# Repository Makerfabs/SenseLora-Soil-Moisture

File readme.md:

SenseLora Soil Moisture
```c++
/*
Version:	    V1.0
Author:		    Yuki
Create Date:	2024/11/20
Note:
*/
```

# Makerfabs

[Makerfabs home page](https://www.makerfabs.com/)

[Makerfabs Wiki](https://wiki.makerfabs.com/)

## Intruduce

Product Link:[SenseLora Soil Moisture](https://www.makerfabs.com/senselora-soil-moisture.html)

Wiki Link : [SenseLora Soil Moisture](https://wiki.makerfabs.com/SenseLora_Soil_Moisture.html)

## Features

Specs:
- ESP32-S3 WROOM module onboard with the WiFi and Bluetooth.
- Detection of soil moisture.
- Arduino Compatible: You can play it with Arduino IDE.
- Onboard LoRa module (433Mhz or 868Mhz or 915Mhz)
- Completely sealed.
- Dustproof waterproof level:IP68.
- Power by 3.7V battery.
- On board MPTT battery charger by solar panel.

# Usage

1.[Usage with LoRa Receiver](https://wiki.makerfabs.com/SenseLora_Soil_Moisture.html#4-usage-with-lora-receiver)

The Lora receiver work with SenseLora modules, it receive LoRa signal around and forward to computer, so the data can be display/record/analyze on PC.

2.[Usage with 4G Gateway](https://wiki.makerfabs.com/SenseLora_Soil_Moisture.html#5-usage-with-4g-gateway)

The 4G LTE CAT1 Gateway work with SenseLora modules, it get the LoRa data and then transmit the data via 4G to cloud server such as TTN, or the monitors phone with SMS.  

## Example

### firmware

Factory test program

### Send data to datacake

Using the Senselora 4G gateway to transfer data to the datacake platform.

### Send data to thingspeak

Using the Senselora 4G gateway to transfer data to the thingspeak platform.

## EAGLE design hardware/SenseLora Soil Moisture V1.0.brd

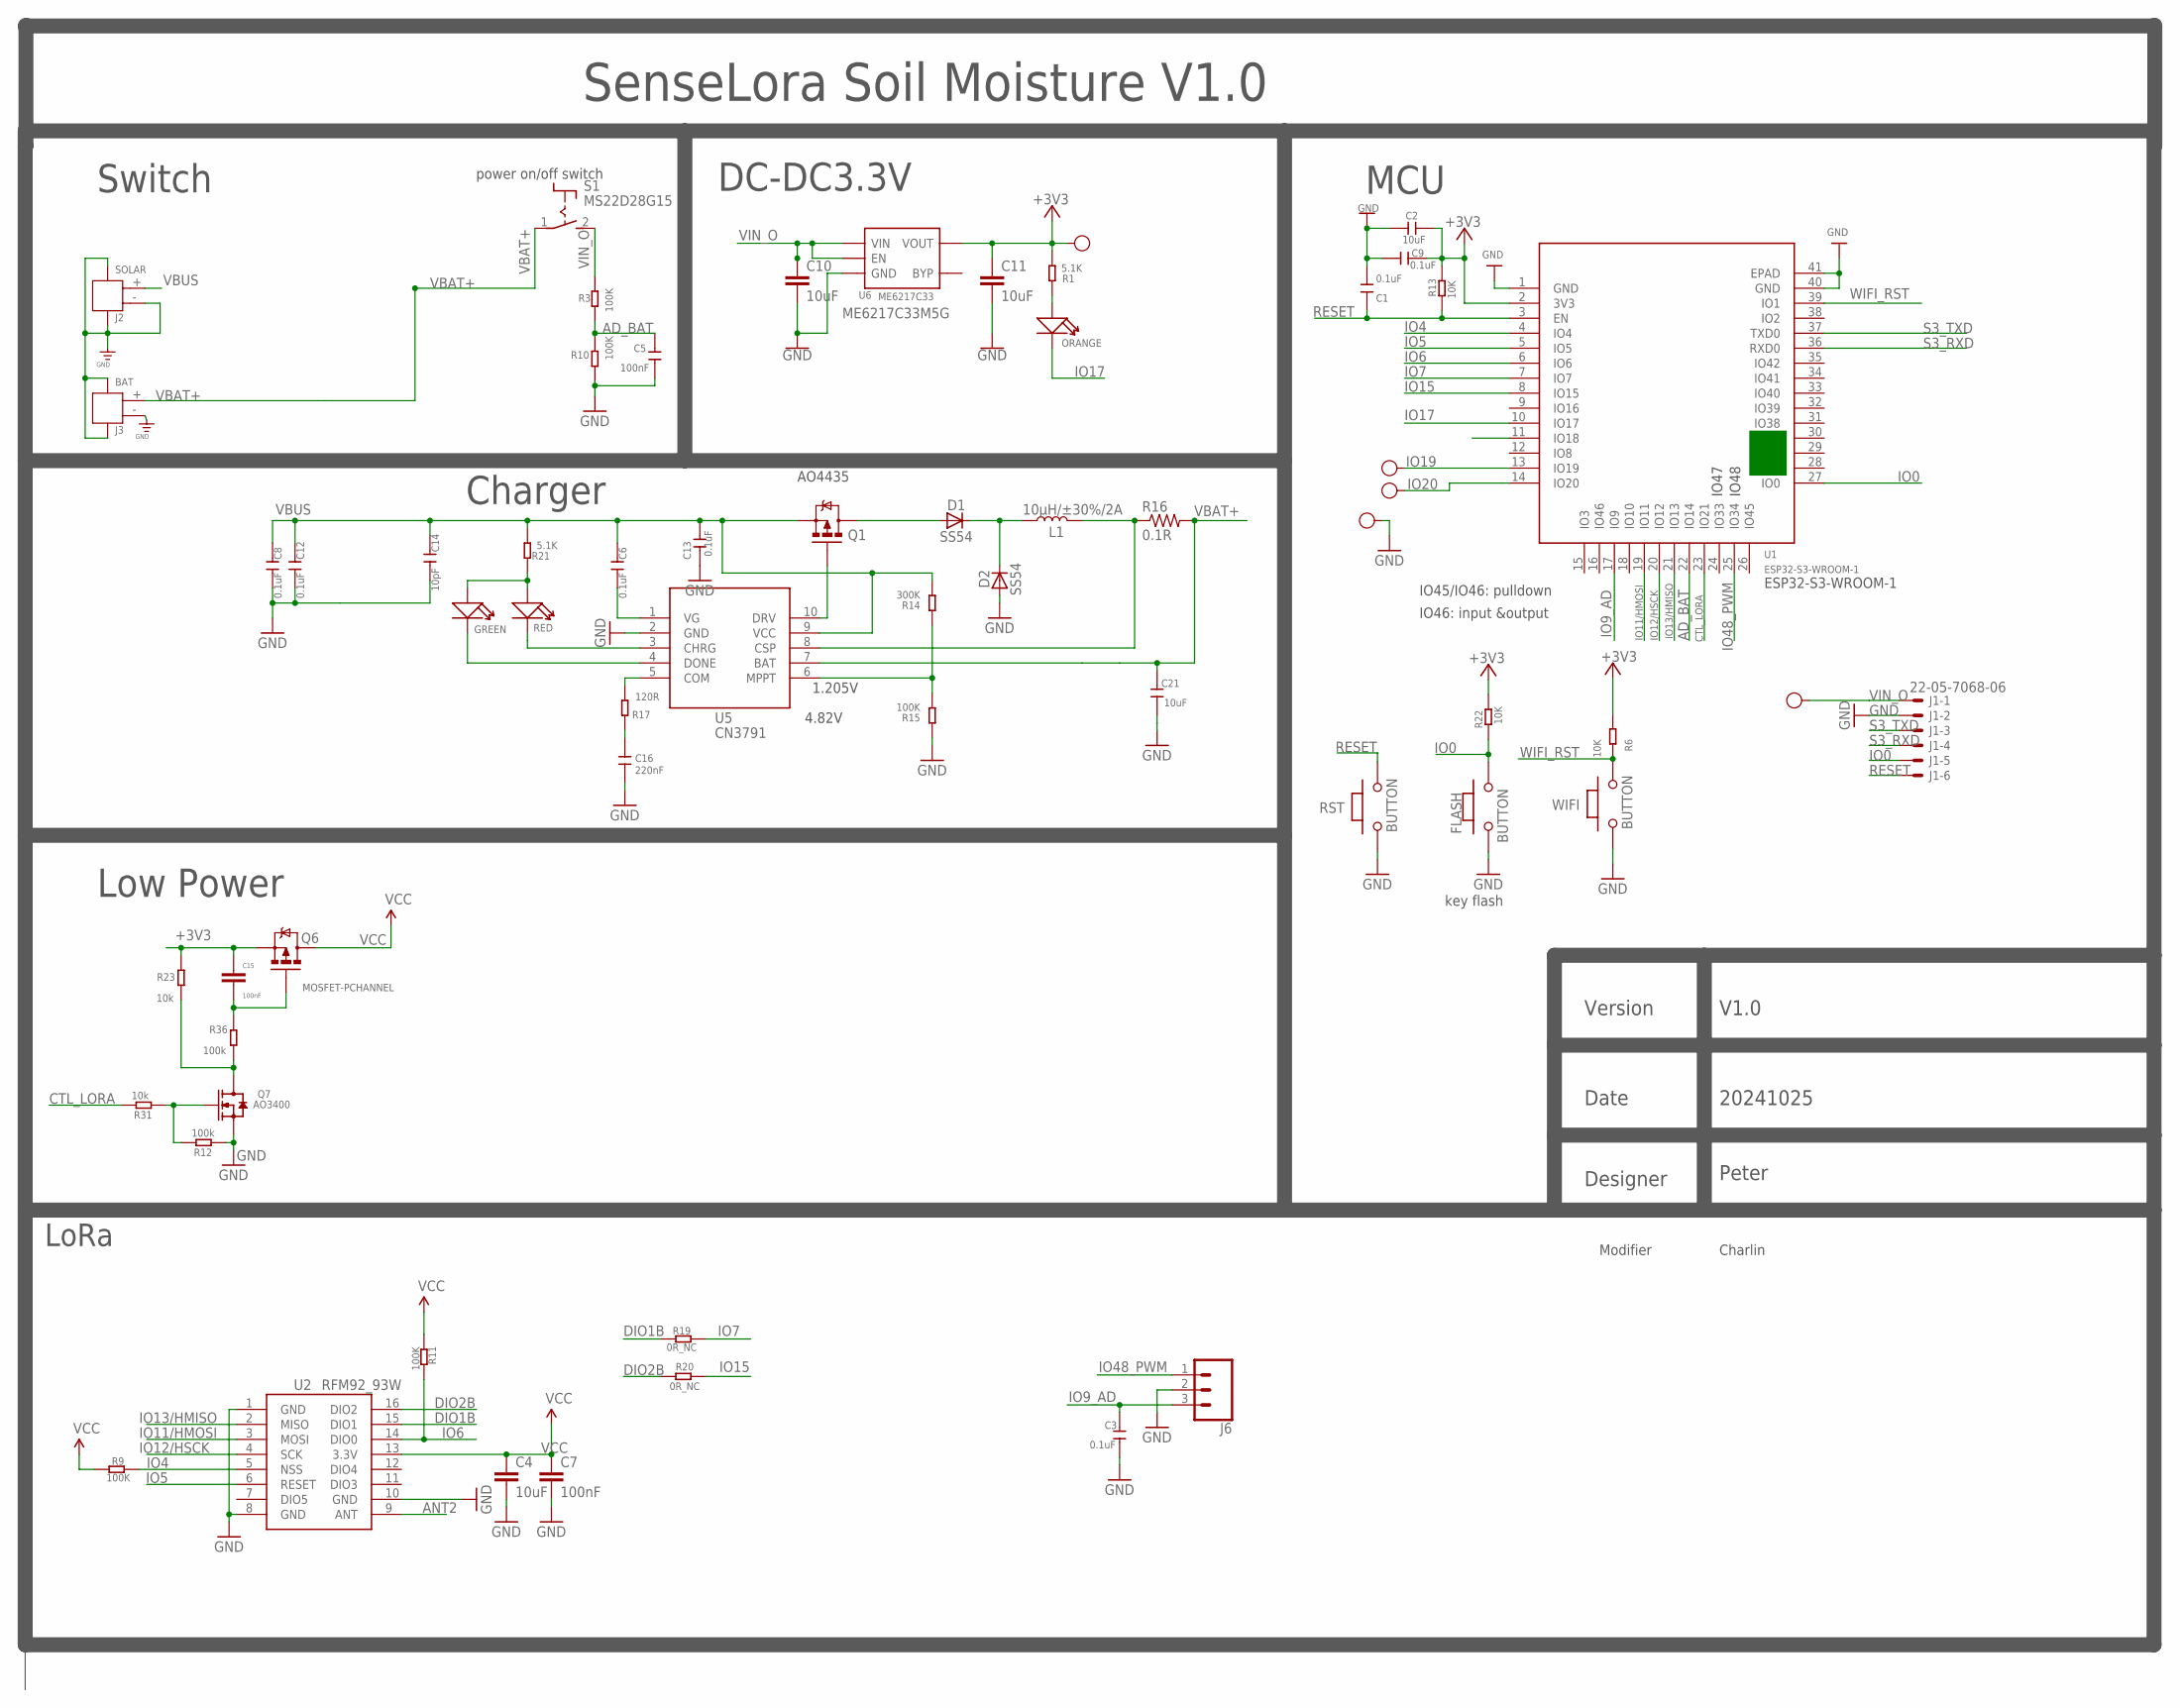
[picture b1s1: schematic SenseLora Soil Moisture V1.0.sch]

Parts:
3V3: TEST-POINT'4545'; TP-D45MIL; PARTNO DNP
C1, C3, C6, C8, C9, C12, C13: 0.1uF; DISCRETE_C0603
C2, C21: 10uF; DISCRETE_C0603
C4, C10, C11: 10uF; C0603
C5, C7, C15: 100nF; C0603
C14: 10pF; DISCRETE_C0603
C16: 220nF; DISCRETE_C0603
CHRG: RED; LED-0603
D1, D2: SS54; DO-214AC
D+: TEST-POINT'4545'; TP-D45MIL; PARTNO DNP
D-: TEST-POINT'4545'; TP-D45MIL; PARTNO DNP
DONE: GREEN; LED-0603
FLASH: BUTTON; 157SW
GND: TEST-POINT'4545'; TP-D45MIL; PARTNO DNP
J1: 22-05-7068-06; 7395-06
J2: SOLAR; HW2-SMD-2.0-90D
J3: BAT; HW2-SMD-2.0-90D
J6: CONN_03SCREW; SCREWTERMINAL-3.5MM-3
L1: 10µH/±30%/2A; CR54
Q1: MOSFET-PCHANNELFDS6675; SO08
Q6: MOSFET-PCHANNEL; SOT23-3
Q7: AO3400; SOT23@1
R1, R21: 5.1K; DISCRETE_R0603
R3, R9, R10, R11: 100K; R0603
R6, R13, R22: 10K; R0603
R12, R36: 100k; R0603
R14: 300K; DISCRETE_R0603
R15: 100K; DISCRETE_R0603
R16: 0.1R; R1206
R17: 120R; DISCRETE_R0603
R19, R20: 0R_NC; R0603
R23, R31: 10k; R0603
RST: BUTTON; 157SW
S1: MS22D28G15; S-MS22D28G15
STA: ORANGE; LED-0603
U1: ESP32-S3-WROOM-1; ESP32-­S2-­SOLO
U2: RFM92_93W
U5: CN3791; SSOP-10-150MIL
U6: ME6217C33; SOT23-5
VI: HP; TP-D45MIL; PARTNO DNP
WIFI: BUTTON; 157SW

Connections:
+3V3: 3V3.T, C2.1, C9.1, C11.1, C15.1, Q6.2 (S), R1.2, R6.2, R13.2, R22.2, R23.2, U1.2 (3V3), U6.5 (VOUT)
AD_BAT: C5.1, R3.2, R10.1, U1.22 (IO14)
ANT2: U2.9 (ANT)
CTL_LORA: R31.2, U1.23 (IO21)
DIO1B: R19.2, U2.15 (DIO1)
DIO2B: R20.2, U2.16 (DIO2)
GND: C1.2, C2.2, C3.2, C4.2, C5.2, C7.2, C8.2, C9.2, C10.2, C11.2, C12.2, C13.1, C14.2, C16.2, C21.2, D2.A, FLASH.1, GND.T, J1.2, J2.3, J2.4, J2.- (2), J3.3, J3.4, J3.- (2), J6.2, Q7.2 (S), R10.2, R12.1, R15.1, RST.1, U1.1 (GND), U1.40 (GND), U1.41 (EPAD), U2.1 (GND), U2.8 (GND), U2.10 (GND), U5.2 (GND), U6.2 (GND), WIFI.1
IO0: FLASH.2, J1.5, R22.1, U1.27 (IO0)
IO4: R9.1, U1.4 (IO4), U2.5 (NSS)
IO5: U1.5 (IO5), U2.6 (RESET)
IO6: R11.1, U1.6 (IO6), U2.14 (DIO0)
IO7: R19.1, U1.7 (IO7)
IO9_AD: C3.1, J6.3, U1.17 (IO9)
IO11/HMOSI: U1.19 (IO11), U2.3 (MOSI)
IO12/HSCK: U1.20 (IO12), U2.4 (SCK)
IO13/HMISO: U1.21 (IO13), U2.2 (MISO)
IO15: R20.1, U1.8 (IO15)
IO17: STA.-, U1.10 (IO17)
IO19: D-.T, U1.13 (IO19)
IO20: D+.T, U1.14 (IO20)
IO48_PWM: J6.1, U1.25 (IO34)
unnamed: R14.1, R15.2, U5.6 (MPPT)
unnamed: Q1.4 (G), U5.10 (DRV)
unnamed: C6.2, U5.1 (VG)
unnamed: D1.C, D2.C, L1.P$1 (1)
unnamed: D1.A, Q1.5 (D), Q1.6 (D), Q1.7 (D), Q1.8 (D)
unnamed: CHRG.+, DONE.+, R21.1
unnamed: DONE.-, U5.4 (DONE)
unnamed: CHRG.-, U5.3 (CHRG)
unnamed: R17.2, U5.5 (COM)
unnamed: C16.1, R17.1
unnamed: R1.1, STA.+
unnamed: C15.2, Q6.1 (G), R36.2
unnamed: Q7.1 (G), R12.2, R31.1
unnamed: L1.P$2 (2), R16.1, U5.8 (CSP)
unnamed: Q7.3 (D), R23.1, R36.1
RESET: C1.1, J1.6, R13.1, RST.2, U1.3 (EN)
S3_RXD: J1.4, U1.36 (RXD0)
S3_TXD: J1.3, U1.37 (TXD0)
VBAT+: C21.1, J3.+ (1), R16.2, S1.1, U5.7 (BAT)
VBUS: C6.1, C8.1, C12.1, C13.2, C14.1, J2.+ (1), Q1.1 (S), Q1.2 (S), Q1.3 (S), R14.2, R21.2, U5.9 (VCC)
VCC: C4.1, C7.1, Q6.3 (D), R9.2, R11.2, U2.13 (3.3V)
VIN_O: C10.1, J1.1, R3.1, S1.2 (S), U6.1 (VIN), U6.3 (EN), VI.T
WIFI_RST: R6.1, U1.39 (IO1), WIFI.2

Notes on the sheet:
DC-DC3.3V
ME6217C33M5G
Charger
LoRa
power on/off switch
key flash
Switch
MCU
Low Power
IO45/IO46: pulldown
IO46: input &output
ESP32-S3-WROOM-1
IO47
IO48
Version
Date
Designer
V1.0
20241025
Peter
SenseLora Soil Moisture V1.0
1.205V
4.82V
Modifier
Charlin
AO4435

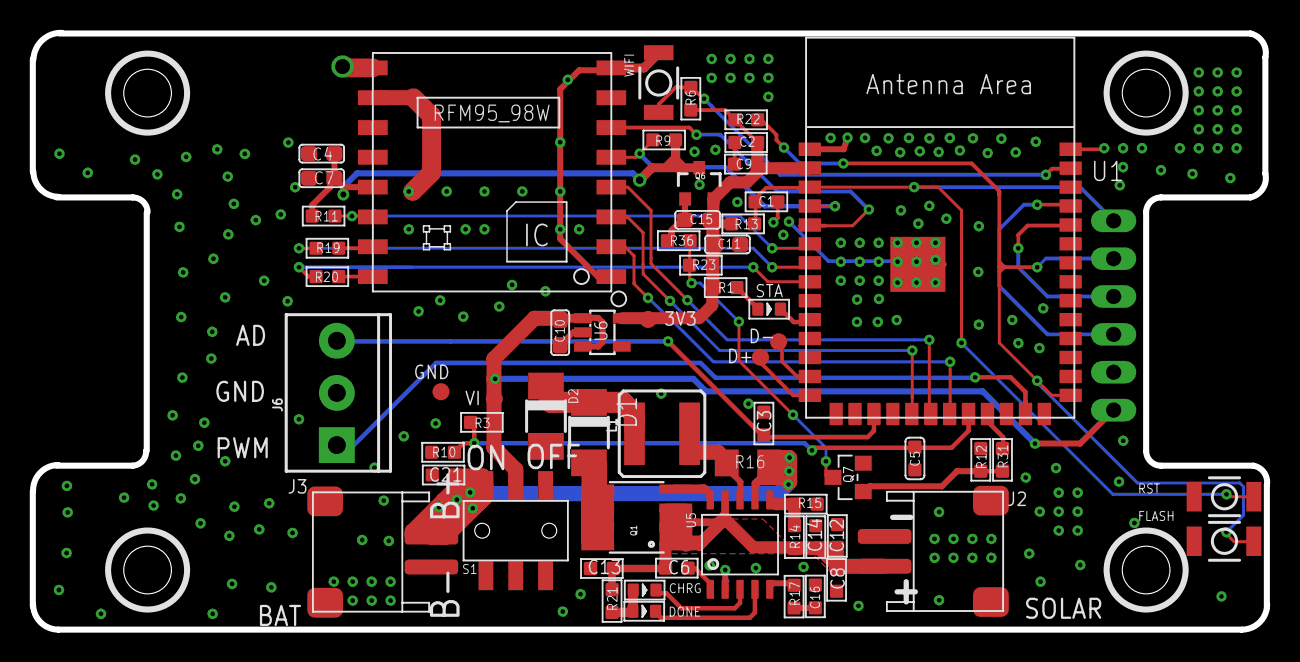
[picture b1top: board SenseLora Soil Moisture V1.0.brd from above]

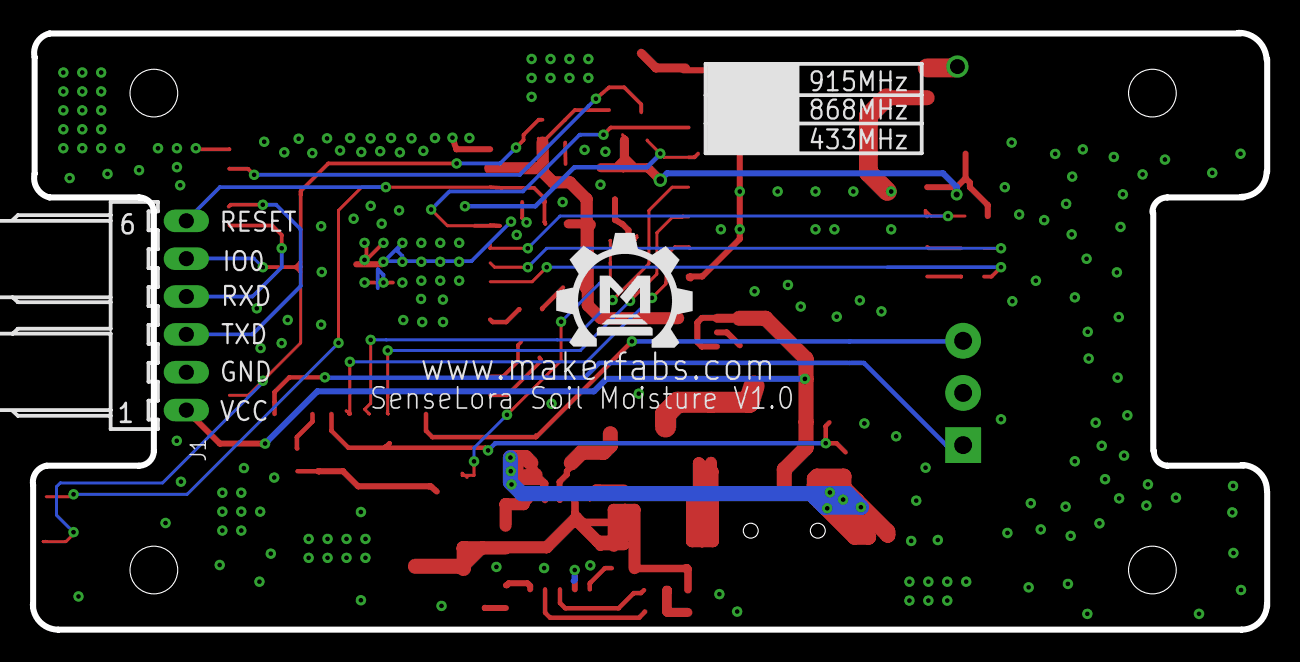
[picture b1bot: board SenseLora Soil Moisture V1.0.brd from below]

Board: 2 copper layers, 82.8 x 40.0 mm, 63 parts (2 on the bottom side), 43 nets.

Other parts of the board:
U$3: MAKERFABS_0.3

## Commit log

2024-11-14 V1.0
2024-11-20 Add readme

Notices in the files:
parts and their libraries:
User-Submitted: Licensing: Creative Commons ShareAlike 4.0 International - https://creativecommons.org/licenses/by-sa/4.0
microbuilder: This work is placed in the public domain, and may be freely used for commercial and non-commercial work with the following conditions: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
